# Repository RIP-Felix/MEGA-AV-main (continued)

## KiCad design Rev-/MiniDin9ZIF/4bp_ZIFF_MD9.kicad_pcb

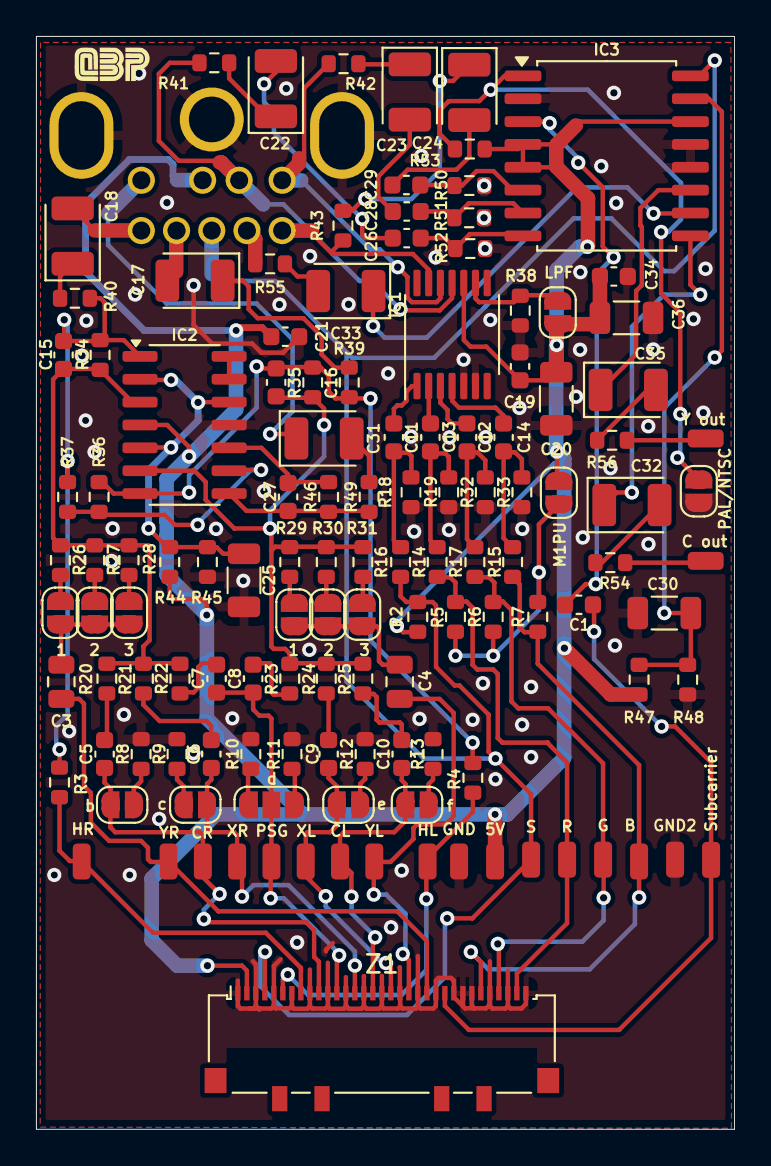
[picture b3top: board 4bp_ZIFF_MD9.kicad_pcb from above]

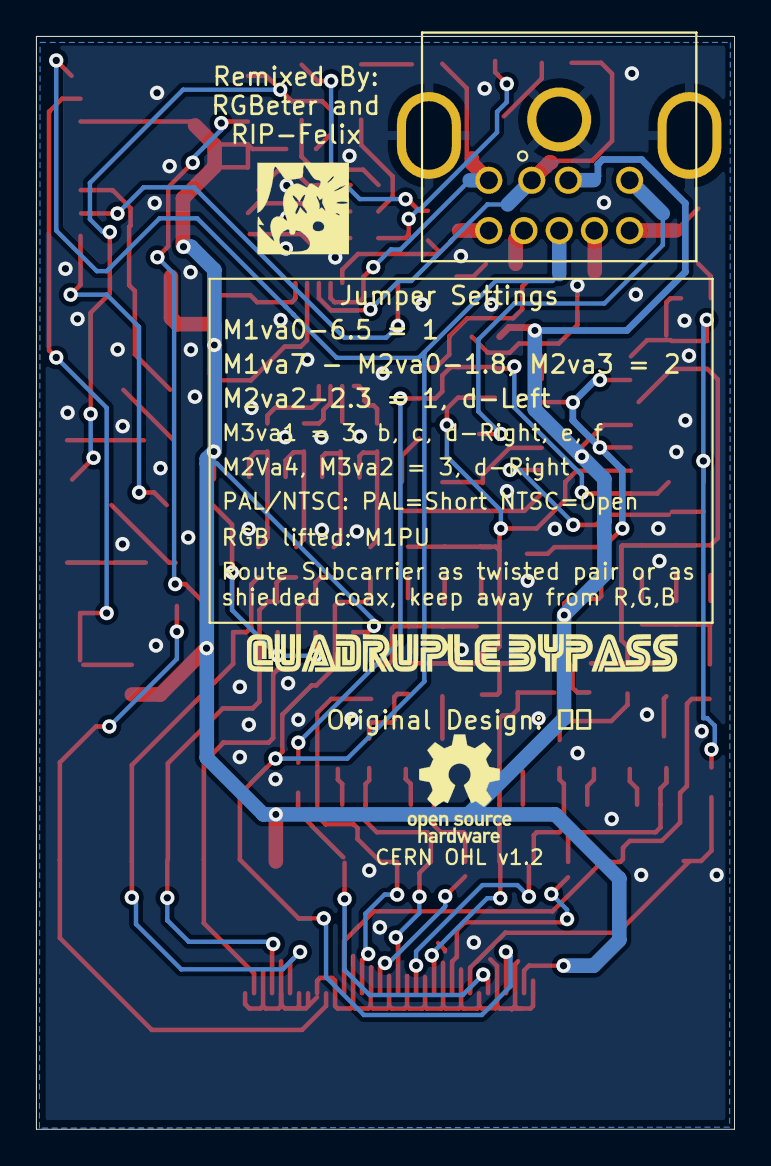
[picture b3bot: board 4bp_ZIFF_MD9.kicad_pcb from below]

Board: 2 copper layers, 38.8 x 60.7 mm, 130 parts (2 on the bottom side), 85 nets.

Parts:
B1: SMD_Conn_01x01; SolderWirePad_1x01_SMD_1x2mm
B2: SolderJumper_2_Open; SolderJumper-2_P1.3mm_Open_RoundedPad1.0x1.5mm
C1, C11, C12, C13, C14, C19, C21, C26, C28, C29, C34: 0.1u; C_0603_1608Metric
C2: SolderJumper_2_Open; SolderJumper-2_P1.3mm_Open_RoundedPad1.0x1.5mm
C3, C4: 10u; C_0805_2012Metric
C5, C6, C7, C8, C9, C10: 1u; C_0603_1608Metric
C15, C16: 150p; C_0603_1608Metric
C17, C18, C31: 47u; CP_EIA-3528-15_AVX-H
C20, C25, C30, C36: 10u; C_1206_3216Metric
C22, C23, C24, C32, C33, C35: 220u; CP_EIA-3528-15_AVX-H
C27: 1nf; C_0603_1608Metric
CL1: SMD_Conn_01x01; SolderWirePad_1x01_SMD_1x2mm
CLKIN1: SMD_Conn_01x01; SolderWirePad_1x01_SMD_1x2mm
CN1: MD-90SM_MD2; MD90SM-MD2
CR1: SMD_Conn_01x01; SolderWirePad_1x01_SMD_1x2mm
D1: SolderJumper_3_Open; SolderJumper-3_P1.3mm_Open_RoundedPad1.0x1.5mm
E1: SolderJumper_2_Open; SolderJumper-2_P1.3mm_Open_RoundedPad1.0x1.5mm
F1: SolderJumper_2_Open; SolderJumper-2_P1.3mm_Open_RoundedPad1.0x1.5mm
G1: SMD_Conn_01x01; SolderWirePad_1x01_SMD_1x2mm
GND1, GND2: SMD_Conn_01x01; SolderWirePad_1x01_SMD_1x2mm
IC1: THS7374IPWR; TSSOP-14_4.4x5mm_P0.65mm
IC2: TL974; SOIC-14_3.9x8.7mm_P1.27mm
IC3: AD724; SOIC-16W_7.5x10.3mm_P1.27mm
J1, J2, J4, J5: SMD_Conn_01x01; SolderWirePad_1x01_SMD_1x2mm
J3: SolderJumper_2_Open; SolderJumper-2_P1.3mm_Open_RoundedPad1.0x1.5mm
LPF1: SolderJumper_2_Open; SolderJumper-2_P1.3mm_Open_RoundedPad1.0x1.5mm
M1PU1: SolderJumper_2_Open; SolderJumper-2_P1.3mm_Open_RoundedPad1.0x1.5mm
P1: SMD_Conn_01x01; SolderWirePad_1x01_SMD_1x2mm
R1: SMD_Conn_01x01; SolderWirePad_1x01_SMD_1x2mm
R2, R11: 2.2k; R_0603_1608Metric
R3, R4, R27, R30: 100k; R_0603_1608Metric
R5, R6, R7, R14, R15, R16, R17, R38: 5.62k; R_0603_1608Metric
R8, R9, R12, R13, R41, R42, R43, R50, R51, R52, R54, R55, R56: 75; R_0603_1608Metric
R10: 750; R_0603_1608Metric
R18, R19, R32, R33: 1k; R_0603_1608Metric
R20, R21, R22, R23, R24, R25: 210k; R_0603_1608Metric
R26, R29, R36, R37, R44, R45, R47, R48, R53: 10k; R_0603_1608Metric
R28, R31: 130k; R_0603_1608Metric
R34, R35: 300k; R_0603_1608Metric
R39, R40, R49: 330; R_0603_1608Metric
R46: 5.5k; R_0603_1608Metric
Ref**: LOGO; QBP_LOGO
Ref**#2: LOGO; 4bp_LOGO
S1: SMD_Conn_01x01; SolderWirePad_1x01_SMD_1x2mm
UNK5V1: SMD_Conn_01x01; SolderWirePad_1x01_SMD_1x2mm
XL1: SMD_Conn_01x01; SolderWirePad_1x01_SMD_1x2mm
XR1: SMD_Conn_01x01; SolderWirePad_1x01_SMD_1x2mm
YL1: SMD_Conn_01x01; SolderWirePad_1x01_SMD_1x2mm
YL2, YL3, YL4: SolderJumper_2_Open; SolderJumper-2_P1.3mm_Open_RoundedPad1.0x1.5mm
YR1: SMD_Conn_01x01; SolderWirePad_1x01_SMD_1x2mm
YR2, YR3, YR4: SolderJumper_2_Open; SolderJumper-2_P1.3mm_Open_RoundedPad1.0x1.5mm
Z1: Conn_01x33_Pin; Molex_502244-3330_1x33-1MP_P0.5mm_Horizontal

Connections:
2V5: C25.1, IC2.2 (-), IC2.5 (+), IC2.12 (+), R44.1, R45.2
2V5_IC3: C30.1, IC3.15 (VSYNC), R47.1, R48.2
+5V: C19.1, C20.1, C21.1, C34.1, C36.1, CN1.2 (5V), IC1.10 (VS+), IC2.4 (V+), IC3.4 (APOS), IC3.5 (ENCD), IC3.14 (DPOS), LPF1.2 (B), M1PU1.1 (A), R2.2, R44.2, R47.2, R53.2, UNK5V1.1, Z1.2
/AUD-L: C16.2, IC2.6 (-), R23.2, R24.2, R25.2, R29.2, R30.2, R31.2, R35.1
/AUD-R: C15.2, IC2.3 (+), R20.2, R21.2, R22.2, R26.2, R27.2, R28.2, R34.1
/B-IN: B1.1, R7.1, R15.1, Z1.28
/CL: C10.2, CL1.1, F1.1 (A), Z1.16
/CLKI: C1.2, CLKIN1.1, Z1.24
/CR: B2.1 (A), C5.2, CR1.1, Z1.10
/G-IN: G1.1, R6.1, R17.1, Z1.30
/HL: J2.1, R4.1, Z1.6
/HR: J1.1, R3.1, Z1.8
/OUT1: C15.1, IC2.1, R3.2, R34.2, R36.1, R40.1
/OUT2: C16.1, IC2.7, R4.2, R35.2, R37.2, R39.1
/OUT3: C27.1, IC2.8, R46.2, R49.1
/PSG: C7.2, C8.2, D1.2 (C), P1.1, Z1.12
/R-IN: R1.1, R5.1, R14.1, Z1.32
/SL: C17.2, CN1.8 (SL)
/SR: C18.2, CN1.9 (SR)
/SYNC-TTL: CN1.5 (SYNC), IC3.16 (HSYNC), R2.1, R16.1, S1.1, Z1.4
/XL: C9.2, E1.1 (A), XL1.1, Z1.18
/XR: C2.1 (A), C6.2, XR1.1, Z1.14
/YL: C4.2, YL1.1, Z1.20
/YR: C3.2, YR1.1, Z1.22
B-OUT: CN1.1 (B), IC1.11 (CH4_OUT), R41.1
CLK: C1.1, IC3.3 (FIN)
CVBS: CN1.4 (CVBS), R55.1
G-OUT: CN1.3 (G), IC1.12 (CH3_OUT), R42.1
GND: C19.2, C20.2, C21.2, C25.2, C30.2, C34.2, C36.2, CN1.S1 (RTN), CN1.S2 (RTN), CN1.S3 (RTN), GND1.1, GND2.1, IC1.5 (GND), IC1.6 (DISABLE), IC2.11 (V-), IC3.2 (AGND), IC3.12 (SELECT), IC3.13 (DGND), J3.1 (A), R8.2, R9.2, R10.2, R11.2, R12.2, R13.2, R18.1, R19.1, R32.1, R33.1, R38.1, R45.1, R48.1, R50.1, R51.1, R52.1, Z1.1, Z1.3, Z1.5, Z1.7, Z1.9, Z1.11, Z1.13, Z1.15, Z1.17, Z1.19, Z1.21, Z1.23, Z1.25, Z1.26, Z1.27, Z1.29, Z1.31, Z1.33
unnamed: B2.2 (B), R8.1
unnamed: C2.2 (B), R9.1
unnamed: C5.1, R20.1
unnamed: C6.1, R21.1
unnamed: C7.1, R22.1
unnamed: C8.1, R23.1
unnamed: C9.1, R24.1
unnamed: C10.1, R25.1
unnamed: C11.2, R16.2, R18.2
unnamed: C12.2, R17.2, R32.2
unnamed: C13.2, R14.2, R19.2
unnamed: C14.2, R15.2, R33.2
unnamed: C17.1, R39.2
unnamed: C18.1, R40.2
unnamed: C22.1, R41.2
unnamed: C22.2, C26.2
unnamed: C23.1, R42.2
unnamed: C23.2, C28.2
unnamed: C24.1, R43.2
unnamed: C24.2, C29.2
unnamed: C31.2, R49.2
unnamed: C32.2, R54.2
unnamed: C33.2, R55.2
unnamed: C35.2, R56.2
unnamed: C31.1, CN1.6 (MONO)
unnamed: D1.1 (A), R10.1
unnamed: D1.3 (B), R11.1
unnamed: E1.2 (B), R12.1
unnamed: F1.2 (B), R13.1
unnamed: IC1.9 (BYPASS), LPF1.1 (A), R38.2
unnamed: C11.1, IC1.1 (CH1_IN)
unnamed: C13.1, IC1.2 (CH2_IN)
unnamed: C12.1, IC1.3 (CH3_IN)
unnamed: C14.1, IC1.4 (CH4_IN)
unnamed: C27.2, IC2.10 (+), R46.1
unnamed: IC2.9 (-), R36.2, R37.1
unnamed: IC2.13 (-), IC2.14
unnamed: C26.1, IC3.8 (BIN), R52.2
unnamed: C33.1, IC3.10 (COMP)
unnamed: C32.1, IC3.9 (CRMA)
unnamed: C28.1, IC3.7 (GIN), R51.2
unnamed: C35.1, IC3.11 (LUMA)
unnamed: C29.1, IC3.6 (RIN), R50.2
unnamed: IC3.1 (STND), J3.2 (B), R53.1
unnamed: J4.1, R54.1
unnamed: J5.1, R56.1
unnamed: M1PU1.2 (B), R5.2, R6.2, R7.2
unnamed: C4.1, YL2.1 (A), YL3.1 (A), YL4.1 (A)
unnamed: R29.1, YL2.2 (B)
unnamed: R30.1, YL3.2 (B)
unnamed: R31.1, YL4.2 (B)
unnamed: C3.1, YR2.1 (A), YR3.1 (A), YR4.1 (A)
unnamed: R26.1, YR2.2 (B)
unnamed: R27.1, YR3.2 (B)
unnamed: R28.1, YR4.2 (B)
R-OUT: CN1.7 (R), IC1.13 (CH2_OUT), R43.1

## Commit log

2025-03-25 Added v0.2 (MegaAV)
2025-03-25 Silkscreen updated.
2025-03-27 Create Saturn Din folder
2025-03-27 fixed silkscreening, minor trace rerouting, and added PCBA files. Note, these are not final.
2025-03-27 Added MegaAV logo
2025-07-09 Create Comments.txt for beta
2025-07-09 Replace Mega AV Logo with current one
2025-07-09 Modified mega av logo
2025-07-09 teardrops addee and removed some thermal reliefs on the zif conn
2025-07-09 Schematic comments
2025-07-10 Added SL3 and SR3 (Sega CD passthrough)
2025-07-11 Silkscreen improvments
2025-07-11 74HC86 support + silkscreening improvments.
2025-07-26 added 10k pullup to HCT123, silkscreening improvments, GND pad next to SBCR
2025-08-15 optimized luma trap values & PSG fix. Some silscreening to.
2025-08-20 36k 32x gain fix
2025-08-22 Fixed jumper silkscreening
2025-08-31 Added MAV and MA3 Licenses. Edited Readme
2025-10-28 Create text
2025-10-28 fix drc
    connect 2 capacitors to GND
    adjust netclass clearance
2025-10-28 Add .gitignore
    Apply the default KiCAD gitignore file
2025-10-28 warnings
2025-10-28 Export symbols
2025-10-30 Changes to the liscense, readme, and silkscreening.
2025-10-30 Changes to readme.md
2025-10-30 Refactor README for clarity and remove duplicates
    Removed duplicate sentences and clarified contributions to the Mega AV project.
2025-10-30 Update README with clarifications on Mega Amp and Mega AV
    Clarified the distinction between Mega Amp 3 and Mega Audio, emphasizing that they are separate entities. Updated acknowledgments for contributions to the Mega AV project.
2025-10-30 Silkscreen change
2025-10-30 Deal with DRC
2025-10-30 Fix ERC
2025-11-13 Silkscreen fix
2025-11-21 MEGA AV Pro & CE revisions added
2025-11-21 folder name
2025-11-22 MegaAV VA0 CE PCBA updates
2025-11-22 Fixed VA0 errors
